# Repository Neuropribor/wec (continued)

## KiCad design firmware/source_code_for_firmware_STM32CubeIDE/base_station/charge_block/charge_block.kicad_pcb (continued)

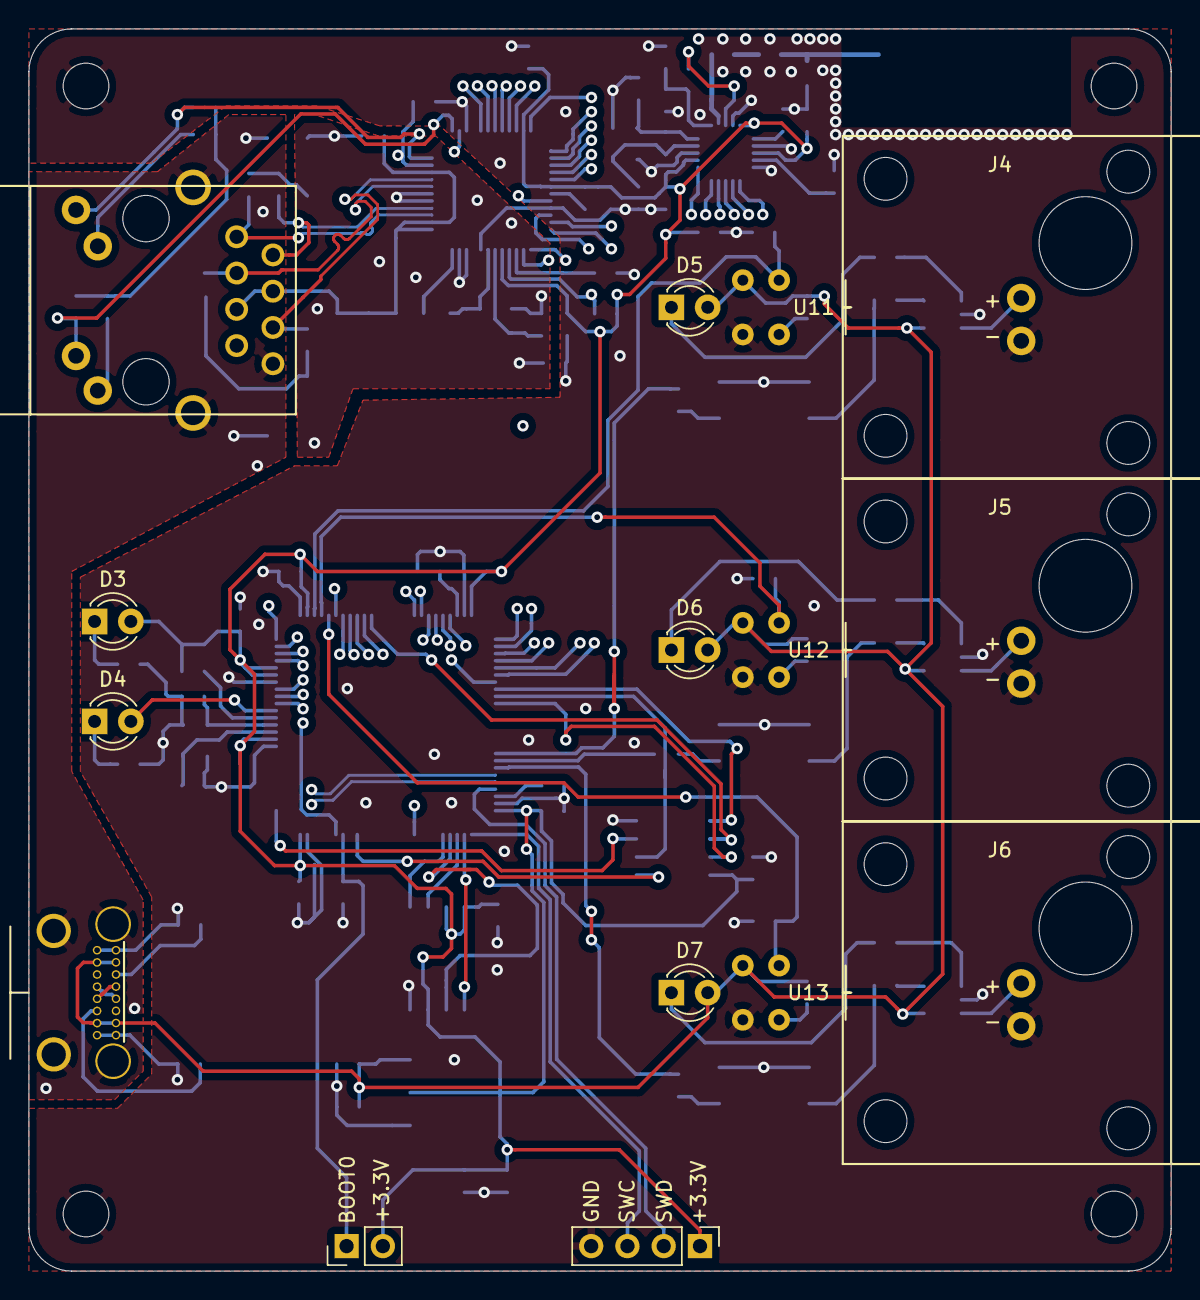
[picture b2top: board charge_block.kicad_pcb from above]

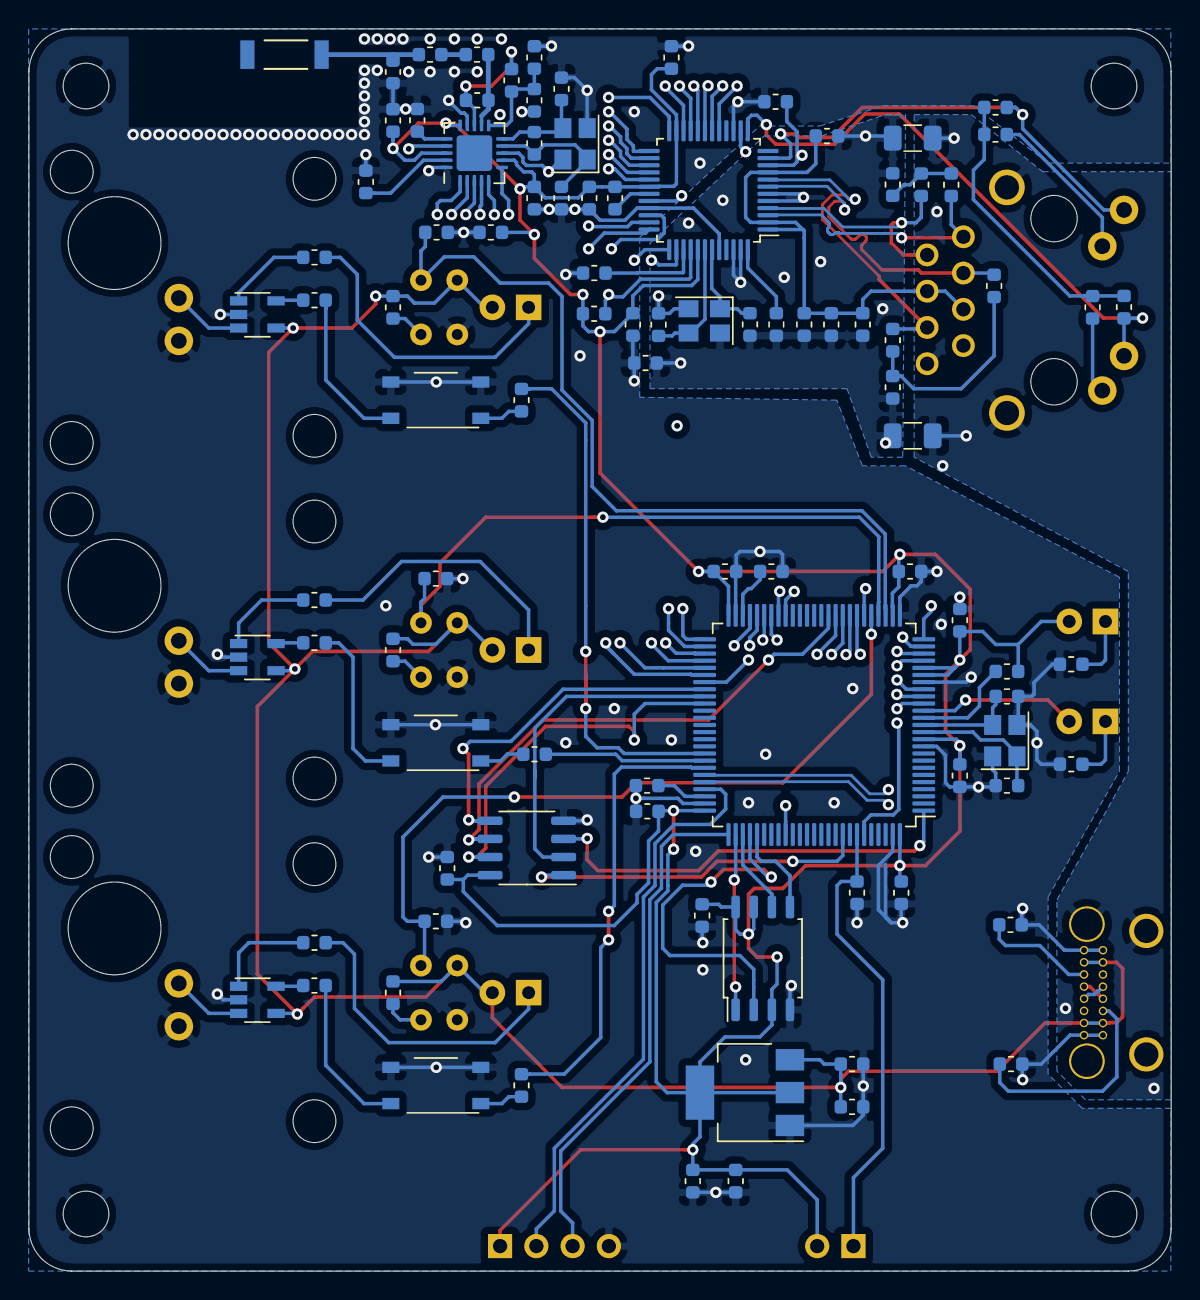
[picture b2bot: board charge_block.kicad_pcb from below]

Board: 4 copper layers, 80.0 x 87.0 mm, 114 parts (95 on the bottom side), 110 nets.
